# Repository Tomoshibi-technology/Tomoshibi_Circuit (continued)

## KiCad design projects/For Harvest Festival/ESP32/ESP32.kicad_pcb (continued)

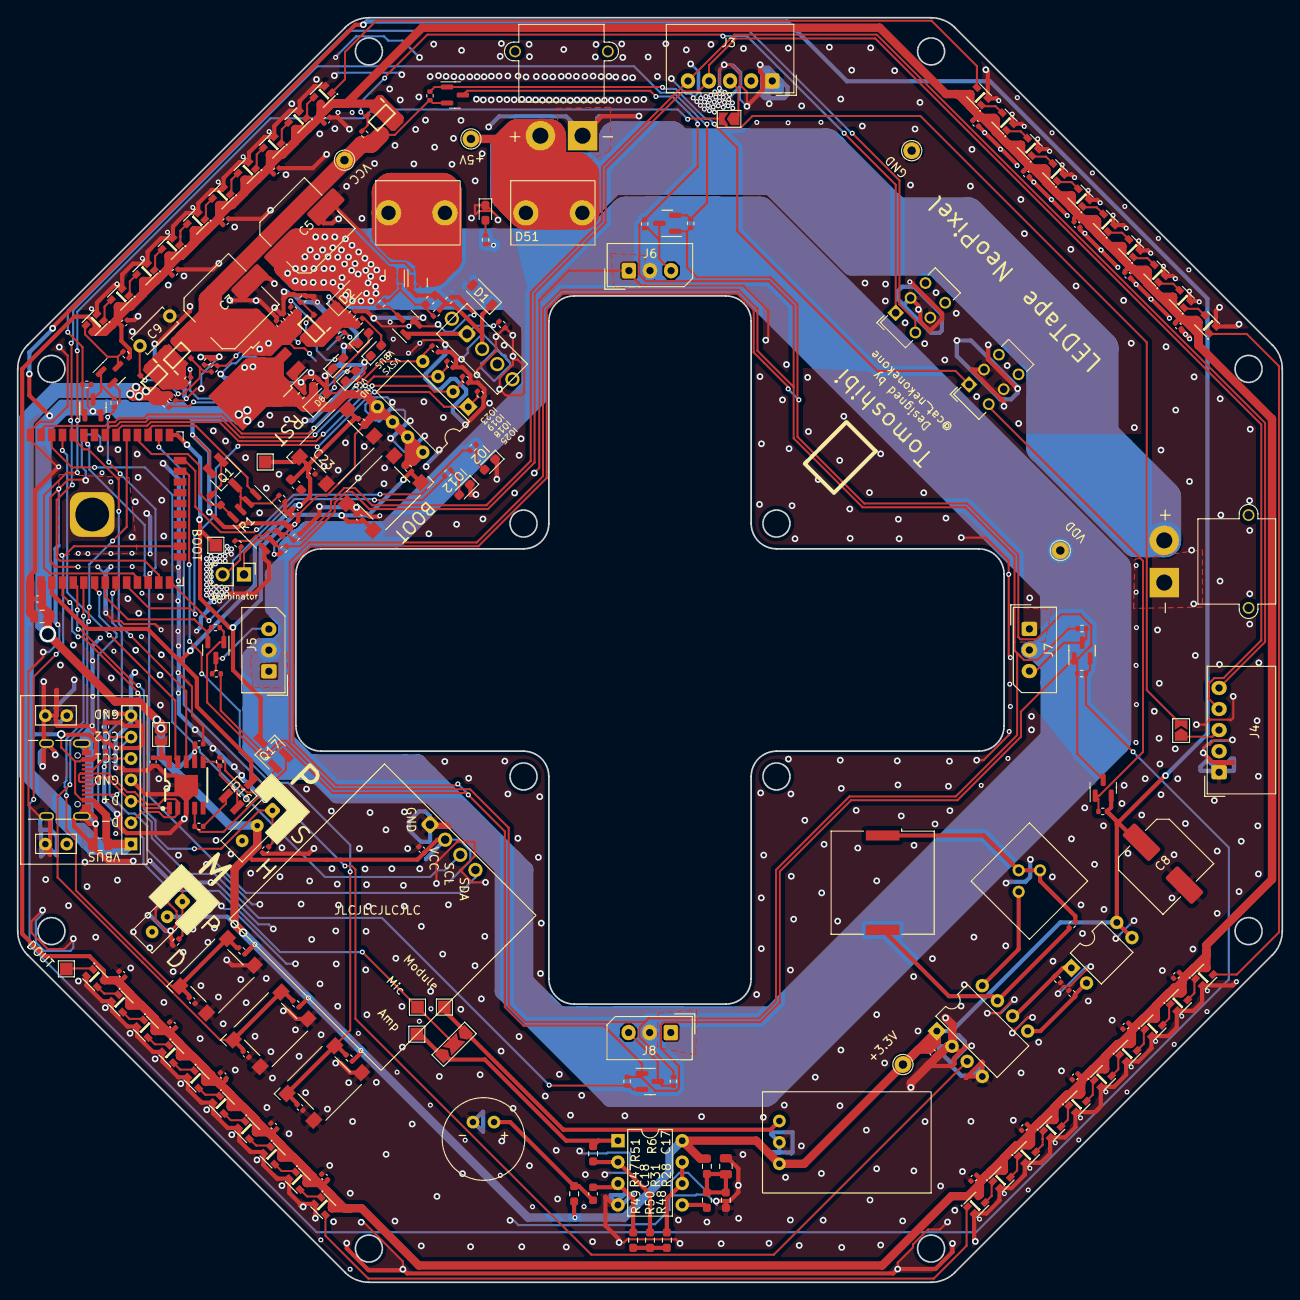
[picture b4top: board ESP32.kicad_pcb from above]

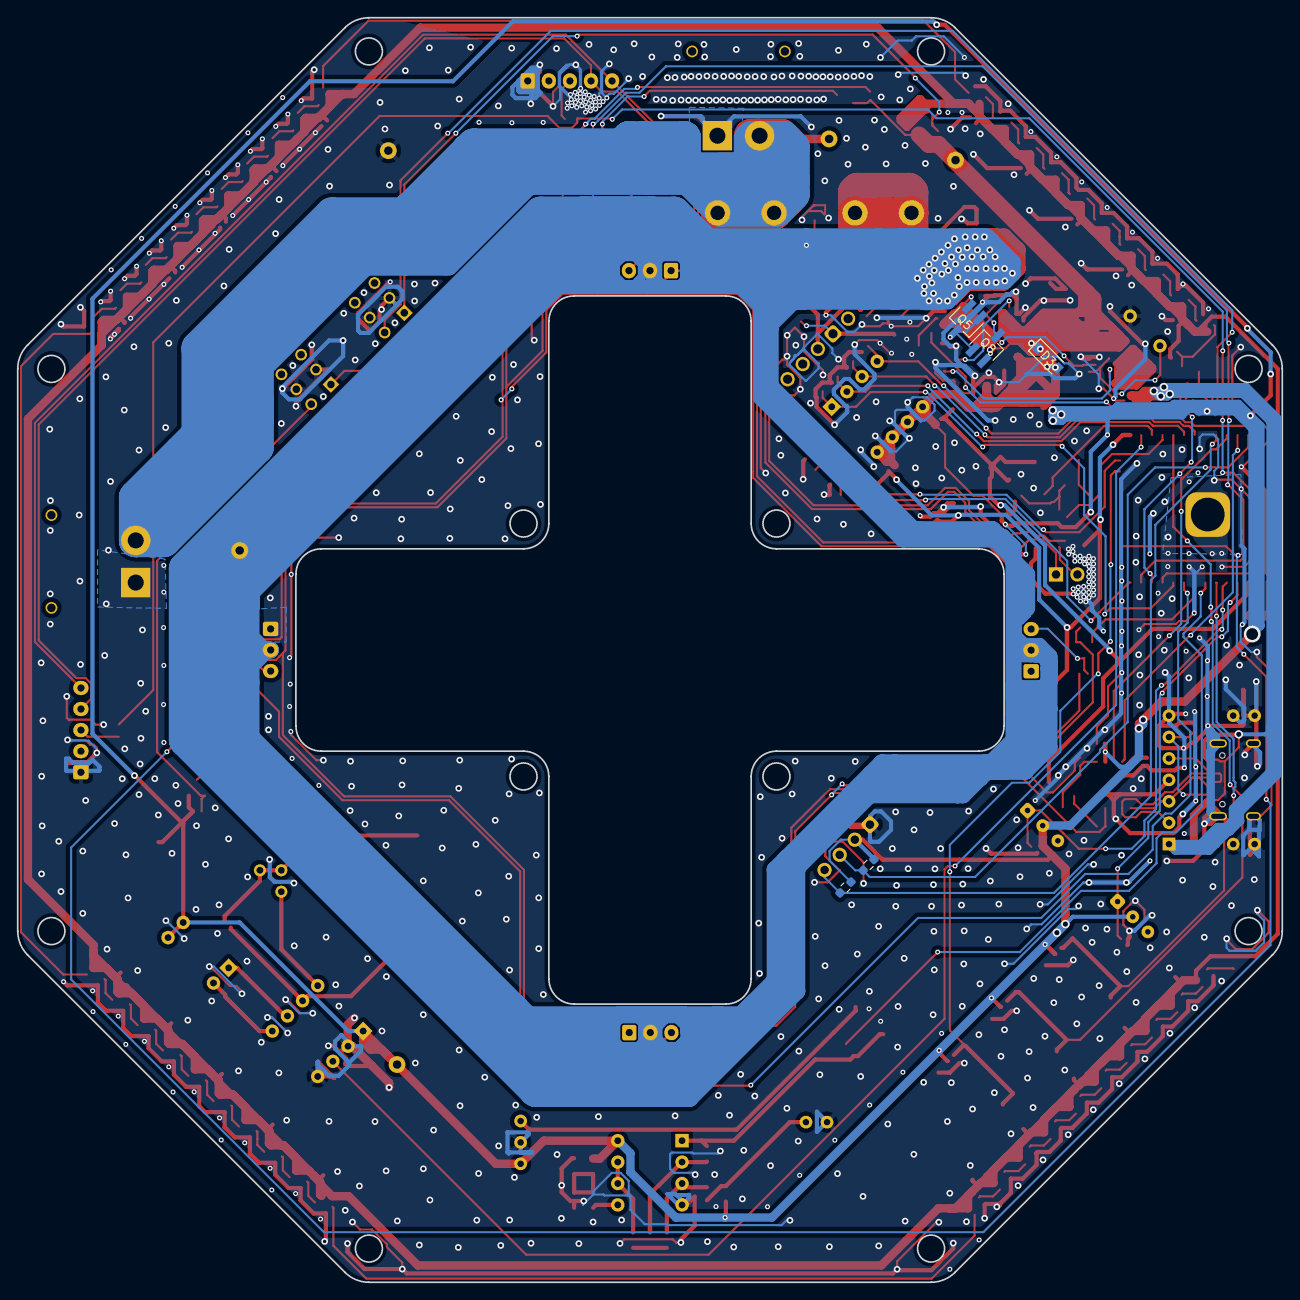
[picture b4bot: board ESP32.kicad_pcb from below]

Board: 2 copper layers, 150.0 x 150.0 mm, 230 parts (5 on the bottom side), 133 nets.

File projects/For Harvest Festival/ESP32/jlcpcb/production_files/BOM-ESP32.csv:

Comment,Designator,Footprint,LCSC
1k,"R12,R17,R20,R21,R22,R23,R25,R29,R30,R67",R_0402_1005Metric,C11702
PMN48XP,"Q2,Q4",UDFN6,C146307
10uF,"C1,C17",C_0805_2012Metric,C15850
4.7uF,"C18,C6",C_0603_1608Metric,C19666
R,"R31,R48",R_0603_1608Metric_Pad0.98x0.95mm_HandSolder,C21189
1k,R50,R_0603_1608Metric_Pad0.98x0.95mm_HandSolder,C21190
7.5k,R1,R_0603_1608Metric,C23234
120,R9,R_0402_1005Metric,C25079
10k,"R10,R11,R13,R14,R15,R16,R18,R19,R24,R26,R27,R32,R35,R36,R37,R38,R39,R40,R41,R42,R43,R44,R45,R46,R5,R52,R53,R54,R55,R56,R57,R58,R59,R60,R61,R62,R63,R64,R65",R_0402_1005Metric,C25744
20k,R3,R_0402_1005Metric,C25765
100k,"R28,R49,R51,R6",R_0603_1608Metric_Pad0.98x0.95mm_HandSolder,C25803
R,"R33,R34",R_0603_1608Metric_Pad0.98x0.95mm_HandSolder,C25804
2.2k,"R7,R8",R_0402_1005Metric,C25879
5.1k,"R2,R4",R_0402_1005Metric,C25905
Q_PMOS_GSD,"Q10,Q11,Q19",SOT-23,C266796
Q_NMOS_GSD,"Q12,Q13,Q14,Q15,Q20,Q3",SOT-23,C2844873
WS2812C-2020-V1,"D11,D12,D13,D14,D15,D16,D17,D18,D19,D20,D21,D22,D23,D24,D25,D26,D27,D28,D29,D30,D31,D32,D33,D34,D35,D36,D37,D38,D39,D40,D41,D42,D43,D44,D45,D46,D47,D48,D49,D50",WS2812C-2020-V1,C2976072
0.1uF,"C13,C14,C15,C16,C2,C20,C21,C22,C24,C25,C26,C27,C28,C29,C3,C30,C31,C32,C33,C34,C35,C36,C37,C38,C39,C4,C40,C41,C42,C43",C_0402_1005Metric,C307331
2.2k,R47,R_0603_1608Metric_Pad0.98x0.95mm_HandSolder,C4190
22uF,C19,C_0805_2012Metric,C45783
1uF,"C10,C11,C12",C_0402_1005Metric,C52923
MAX3485,U1,SOP-8_3.9x4.9mm_P1.27mm,C558792
CH340K,U2,CH340K,C968586
Jumper_2_Open,JP1,PinHeader_1x02_P2.54mm_Vertical,
MountingHole_Pad,H2,TestPoint_Pad_1.5x1.5mm,
MountingHole_Pad,H1,TestPoint_Pad_1.5x1.5mm,
SW_SPST,SW5,SW_SPST_Omron_B3FS-100xP,
Conn_01x03_Female,J7,Molex_SPOX_5267-03A_1x03_P2.50mm_Vertical,
Conn_01x03_Female,J5,Molex_SPOX_5267-03A_1x03_P2.50mm_Vertical,
Q_NPN_BEC,Q17,SC-59_Handsoldering,
MountingHole_Pad,H7,TestPoint_Pad_1.5x1.5mm,
LED,D10,LED_0603_1608Metric_Pad1.05x0.95mm_HandSolder,
Conn_01x05_Female,J3,Molex_SPOX_5268-05A_1x05_P2.50mm_Horizontal,
SW_SPST,SW7,SW_SPST_Omron_B3FS-100xP,
LED,D9,LED_0603_1608Metric_Pad1.05x0.95mm_HandSolder,
LED,D7,LED_0603_1608Metric_Pad1.05x0.95mm_HandSolder,
PMN48XP,Q7,SSM6J808R,
D,D1,D_SOD-123,
MountingHole_Pad,H5,TestPoint_Pad_1.5x1.5mm,
LED,D4,LED_0603_1608Metric_Pad1.05x0.95mm_HandSolder,
AE-MICAMP,U7,AE-MICAMP,
470uF,C8,C_Elec_8x10.2,
Speaker,LS1,Buzzer_Murata_PKLCS1212E,
ADJ_ST,C9,C_Disc_D5.0mm_W2.5mm_P5.00mm,
Jumper_2_Open,JP3,SolderJumper-2_P1.3mm_Open_TrianglePad1.0x1.5mm,
Conn_01x02_Female,J9,AMASS_XT30PW-M_1x02_P2.50mm_Horizontal,
SW_DIP_x04,SW11,DIP-8_W7.62mm,
Conn_01x05_Female,J4,Molex_SPOX_5268-05A_1x05_P2.50mm_Horizontal,
Microphone_Condenser,MK1,C9767,
SW_DIP_x02,SW2,DIP-4_W7.62mm,
Q_NPN_BEC,Q16,SC-59_Handsoldering,
D_Zener,D8,D_SOD-323_HandSoldering,
TestPoint,TP5,TestPoint_THTPad_D2.0mm_Drill1.0mm,
NJM4558,U6,DIP-8_W7.62mm,
TestPoint,TP4,TestPoint_THTPad_D2.0mm_Drill1.0mm,
Jumper_2_Open,JP4,SolderJumper-2_P1.3mm_Open_TrianglePad1.0x1.5mm,
C,C23,C_0603_1608Metric_Pad1.08x0.95mm_HandSolder,
LED,D6,LED_0603_1608Metric_Pad1.05x0.95mm_HandSolder,
SW_SPDT,SW3,3P_SPDT_SlideSwitch,
470uF,C5,C_Elec_8x10.2,
R_Potentiometer,RV1,TSR-3386K,
USB_C_Receptacle_USB2.0,J10,USB_C_Receptacle_GCT_USB4105-xx-A_16P_TopMnt_Horizontal,
TestPoint,TP3,TestPoint_THTPad_D2.0mm_Drill1.0mm,
MountingHole_Pad,H8,TestPoint_Pad_1.5x1.5mm,
Jumper_2_Open,JP2,SolderJumper-2_P1.3mm_Open_TrianglePad1.0x1.5mm,
Conn_01x03_Female,J8,Molex_SPOX_5267-03A_1x03_P2.50mm_Vertical,
Q_PNP_BEC,Q1,SC-59_Handsoldering,
TestPoint,TP1,TestPoint_THTPad_D2.0mm_Drill1.0mm,
OLED_akitsuki,U5,128×64_OLED_White,
SW_SPST,SW10,SW_SPST_Omron_B3FS-100xP,
TestPoint,TP2,TestPoint_THTPad_D2.0mm_Drill1.0mm,
SW_SPDT,SW1,3P_SPDT_5Pin_ToggleSwitch,
ESP32-WROOM-32,U8,ESP32-WROOM-32,
SW_SPST,SW6,SW_SPST_Omron_B3FS-100xP,
MountingHole_Pad,H6,TestPoint_Pad_1.5x1.5mm,
AMS1117CD-3.3,U3,TO-252-3_TabPin2,
Fuse,F1,FUC_03A,
USB_C_Receptacle_USB2.0,J1,USB_C(simple),
470uF,C7,C_Elec_8x10.2,
Conn_01x03_Female,J6,Molex_SPOX_5267-03A_1x03_P2.50mm_Vertical,
LED,D51,LED_0603_1608Metric_Pad1.05x0.95mm_HandSolder,
SolderJumper_3_Open,JP5,SolderJumper-3_P2.0mm_Open_TrianglePad1.0x1.5mm_NumberLabels,
Conn_01x02_Female,J2,AMASS_XT30PW-M_1x02_P2.50mm_Horizontal,
SW_DPDT_x2,SW8,SW_CuK_JS202011CQN_DPDT_Straight,
LED,D5,LED_0603_1608Metric_Pad1.05x0.95mm_HandSolder,
SW_SPDT,SW4,3P_SPDT_SlideSwitch,
NJU72501_Module,U4,DIP-8_W7.62mm,
PMN48XP,Q18,SSM6J808R,
D_Schottky,D2,D_SOD-123,
SW_DPDT_x2,SW12,SW_CuK_JS202011CQN_DPDT_Straight,
PMN48XP,Q6,SSM6J808R,
SW_SPST,SW9,SW_SPST_Omron_B3FS-100xP,
PMN48XP,Q9,SSM6J808R,
Q_PNP_BEC,Q8,SC-59_Handsoldering,
Q_PNP_BEC,Q5,SC-59_Handsoldering,
D,D3,D_SOD-123,

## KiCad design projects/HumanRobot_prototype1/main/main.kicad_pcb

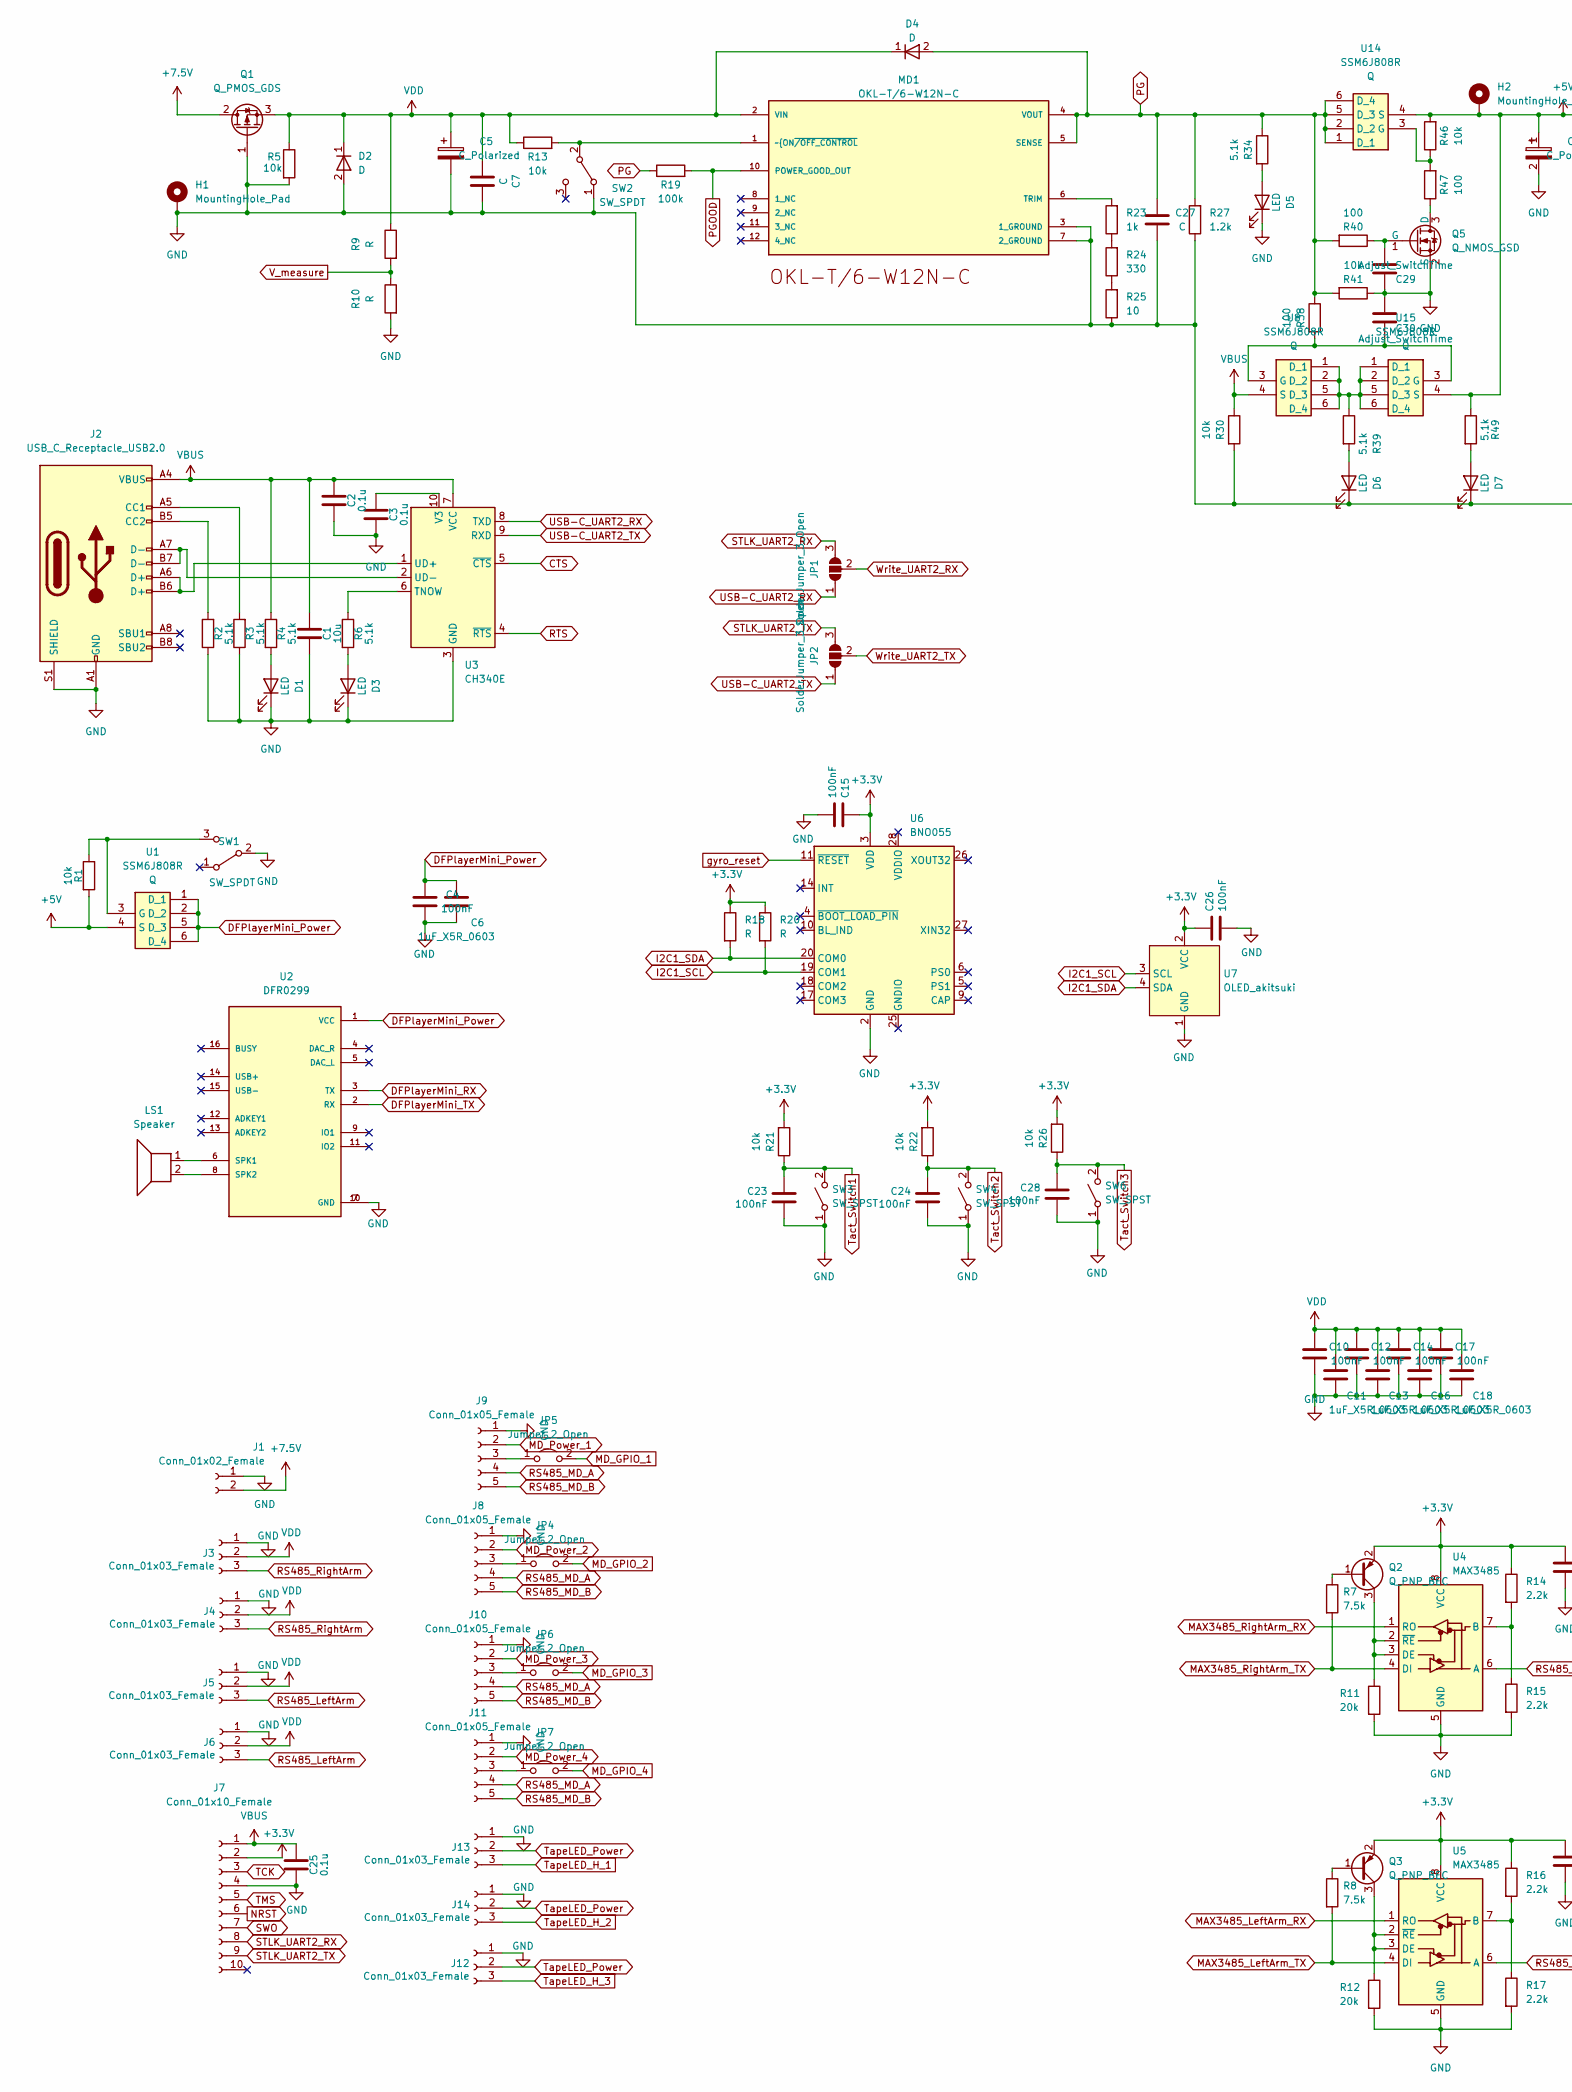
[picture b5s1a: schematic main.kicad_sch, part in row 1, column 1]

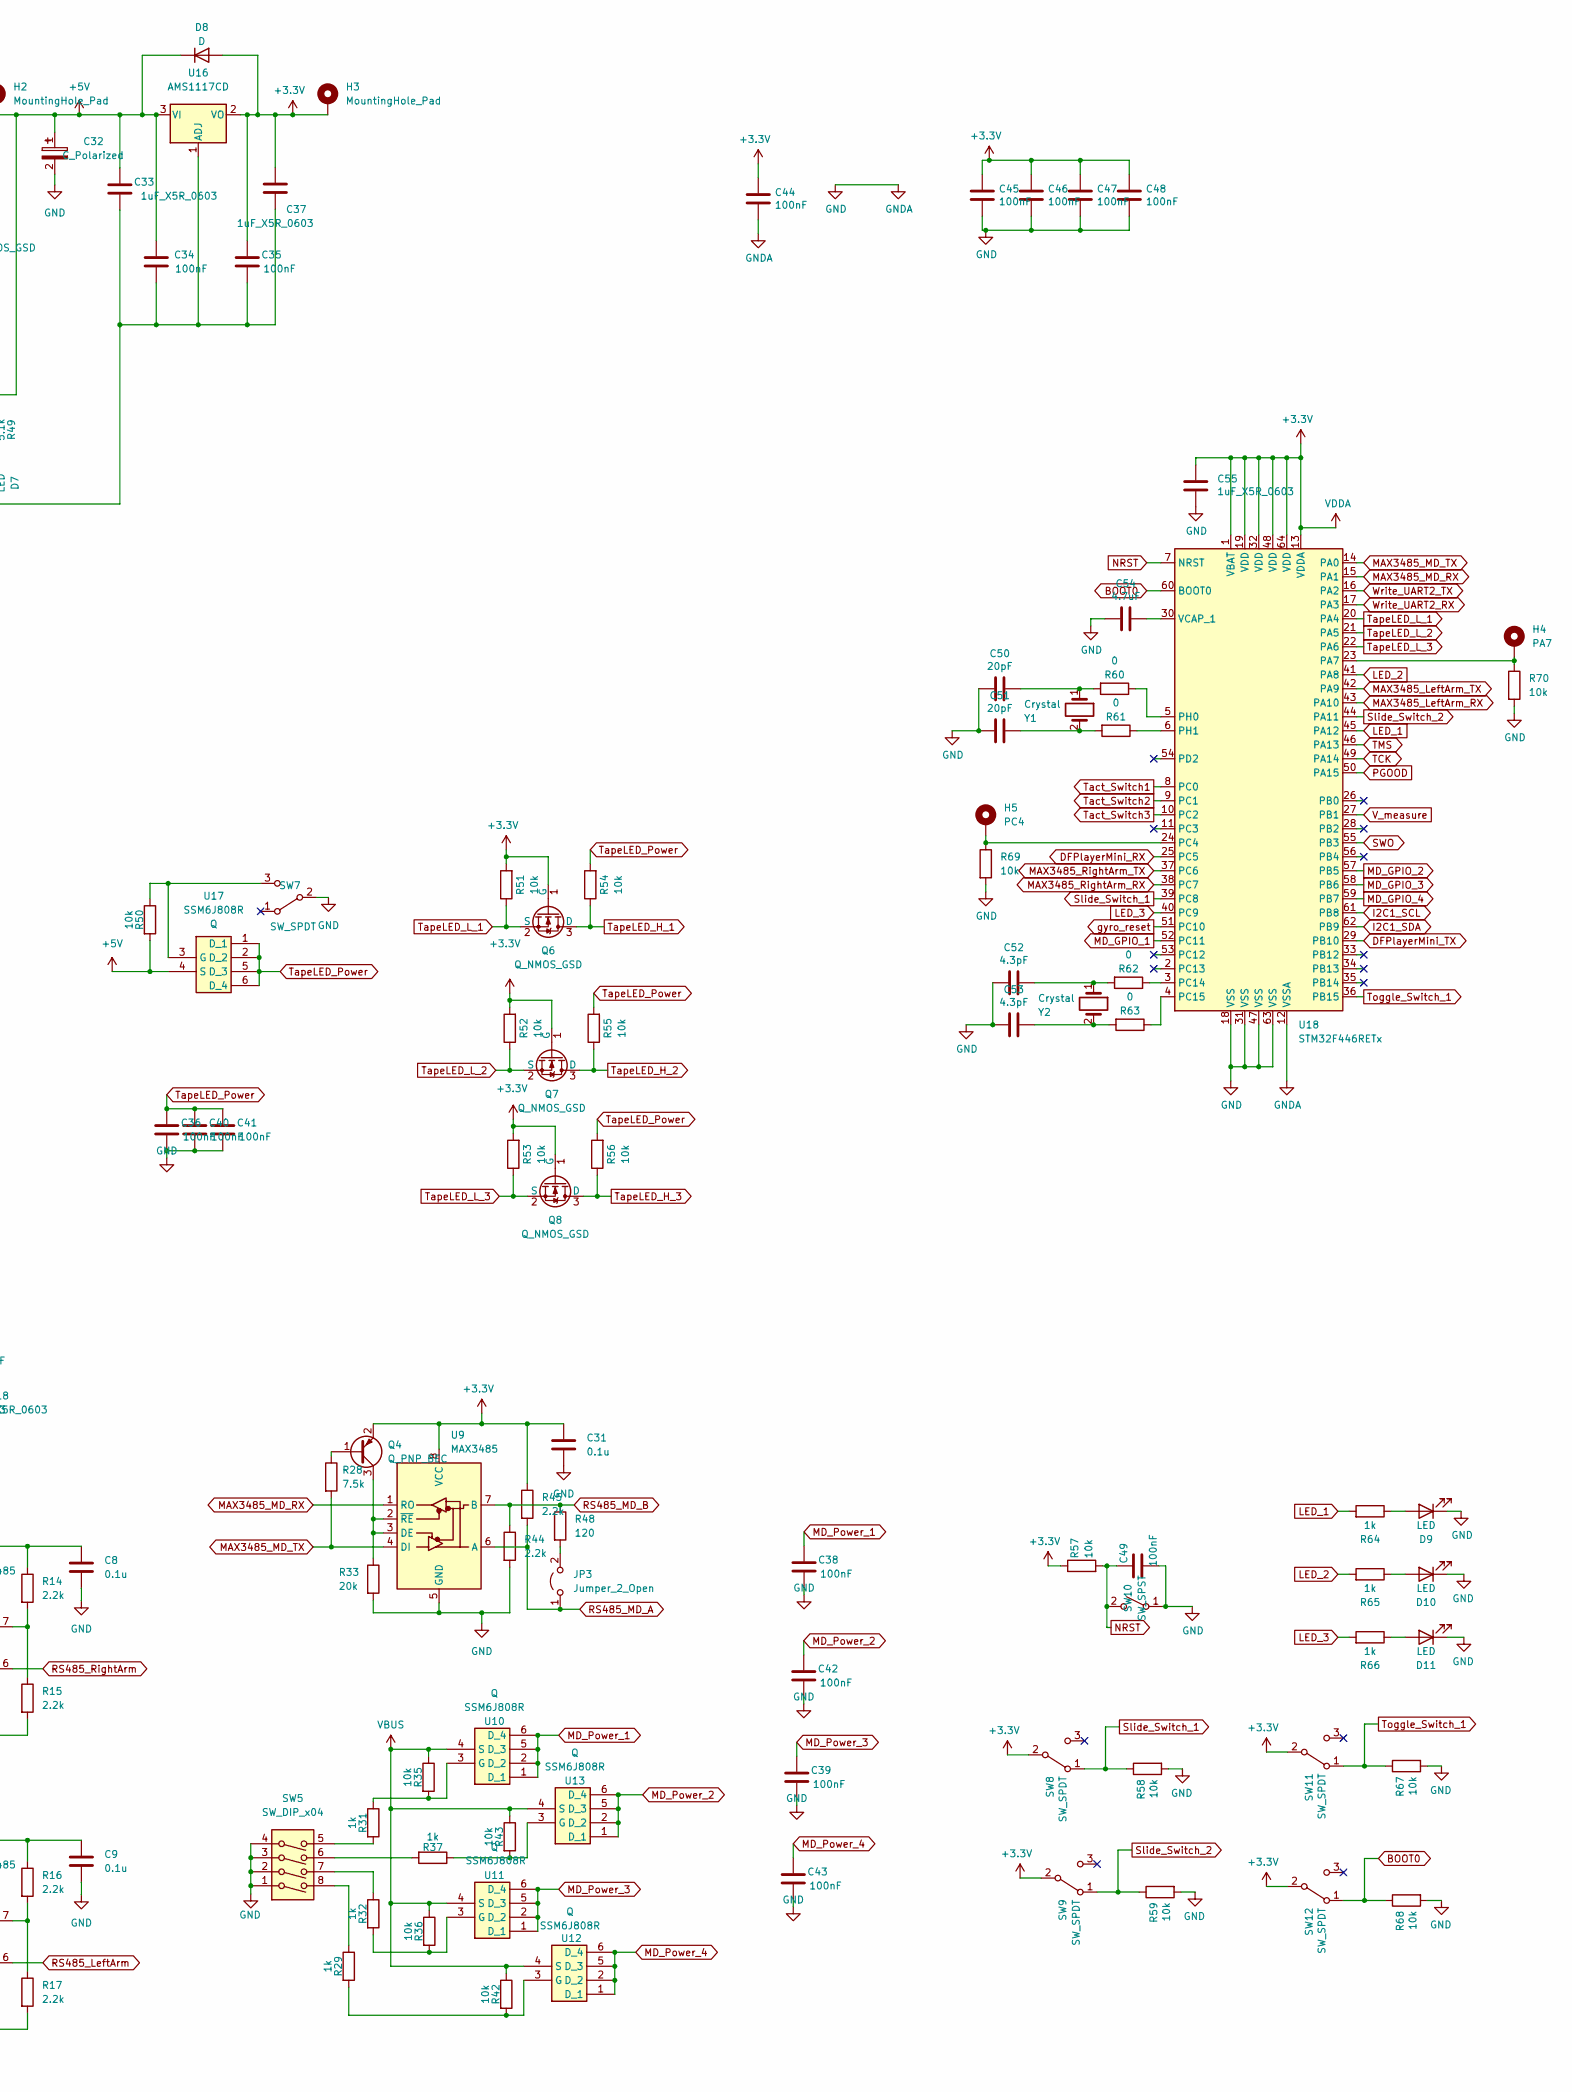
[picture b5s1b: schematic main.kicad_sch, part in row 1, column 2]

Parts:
C1: 10u; C_0805_2012Metric_Pad1.18x1.45mm_HandSolder
C2, C3, C8, C9, C25, C31: 0.1u; C_0603_1608Metric_Pad1.08x0.95mm_HandSolder
C4, C10, C12, C14, C15, C17, C23, C24, C26, C28, C34, C35, C36, C38, C39, C40, C41, C42, C43, C44, C45, C46, C47, C48, C49: 100nF; C_0603_1608Metric_Pad1.08x0.95mm_HandSolder
C5, C32: C_Polarized; C_Elec_8x10.2
C6, C11, C13, C16, C18, C33, C37, C55: 1uF_X5R_0603; C_0603_1608Metric_Pad1.08x0.95mm_HandSolder
C7: C; CAPC3225X270N
C27: C; CAPC3216X180N
C29, C30: Adjust_SwitchTime; C_Disc_D5.0mm_W2.5mm_P5.00mm
C50, C51: 20pF; C_Disc_D5.0mm_W2.5mm_P5.00mm
C52, C53: 4.3pF; C_Disc_D5.0mm_W2.5mm_P5.00mm
C54: 4.7uF; C_0805_2012Metric_Pad1.18x1.45mm_HandSolder
D1, D3, D5, D6, D7, D9, D10, D11: LED; LED_0603_1608Metric_Pad1.05x0.95mm_HandSolder
D2, D4, D8: D; D_SOD-123
H1, H2, H3: MountingHole_Pad; TestPoint_Pad_3.0x3.0mm
H4: PA7; TestPoint_Pad_3.0x3.0mm
H5: PC4; TestPoint_Pad_3.0x3.0mm
J1: Conn_01x02_Female; AMASS_XT30PW-M_1x02_P2.50mm_Horizontal
J2: USB_C_Receptacle_USB2.0; USB_C(simple)
J3, J4, J5, J6, J12, J13, J14: Conn_01x03_Female; Molex_SPOX_5268-03A_1x03_P2.50mm_Horizontal
J7: Conn_01x10_Female; IDC-Header_2x05_P2.54mm_Horizontal
J8, J9, J10, J11: Conn_01x05_Female; Molex_SPOX_5268-05A_1x05_P2.50mm_Horizontal
JP1, JP2: SolderJumper_3_Open; SolderJumper-3_P2.0mm_Open_TrianglePad1.0x1.5mm_NumberLabels
JP3: Jumper_2_Open; PinHeader_1x02_P2.54mm_Vertical
JP4, JP5, JP6, JP7: Jumper_2_Open; SolderJumper-2_P1.3mm_Open_TrianglePad1.0x1.5mm
LS1: Speaker; Buzzer_Murata_PKMCS0909E
MD1: OKL-T/6-W12N-C; MURATA_OKL-T-6-W12N-C; MOUSER_PART_NUMBER 580-OKL-T/6-W12N-C
Q1: Q_PMOS_GDS; TO-251-3_Vertical
Q2, Q3, Q4: Q_PNP_BEC; SC-59
Q5, Q6, Q7, Q8: Q_NMOS_GSD; SOT-23_Handsoldering
R1, R5, R13, R21, R22, R26, R30, R35, R36, R41, R42, R43, R46, R50, R51, R52, R53, R54, R55, R56, R57, R58, R59, R67, R68, R69, R70: 10k; R_0603_1608Metric_Pad0.98x0.95mm_HandSolder
R2, R3, R4, R6, R34, R39, R49: 5.1k; R_0603_1608Metric_Pad0.98x0.95mm_HandSolder
R7, R8, R28: 7.5k; R_0603_1608Metric_Pad0.98x0.95mm_HandSolder
R9, R10, R18, R20: R; R_0603_1608Metric_Pad0.98x0.95mm_HandSolder
R11, R12, R33: 20k; R_0603_1608Metric_Pad0.98x0.95mm_HandSolder
R14, R15, R16, R17, R44, R45: 2.2k; R_0603_1608Metric_Pad0.98x0.95mm_HandSolder
R19: 100k; R_0603_1608Metric_Pad0.98x0.95mm_HandSolder
R23, R29, R31, R32, R37, R64, R65, R66: 1k; R_0603_1608Metric_Pad0.98x0.95mm_HandSolder
R24: 330; R_0603_1608Metric_Pad0.98x0.95mm_HandSolder
R25: 10; R_0603_1608Metric_Pad0.98x0.95mm_HandSolder
R27: 1.2k; R_0603_1608Metric_Pad0.98x0.95mm_HandSolder
R38, R40, R47: 100; R_0603_1608Metric_Pad0.98x0.95mm_HandSolder
R48: 120; R_0603_1608Metric_Pad0.98x0.95mm_HandSolder
R60, R61, R62, R63: 0; R_0603_1608Metric_Pad0.98x0.95mm_HandSolder
SW1, SW2, SW7, SW8, SW9, SW12: SW_SPDT; 3P_SPDT_SlideSwitch
SW3, SW4, SW6, SW10: SW_SPST; SW_SPST_Omron_B3FS-100xP
SW5: SW_DIP_x04; DIP-8_W7.62mm
SW11: SW_SPDT; 3P_SPDT_5Pin_ToggleSwitch
U1, U8, U10, U11, U12, U13, U14, U15, U17: SSM6J808R; Mouser Part Number 757-SSM6K809RLXHF
U2: DFR0299; MODULE_DFR0299
U3: CH340E; MSOP-10_3x3mm_P0.5mm
U4, U5, U9: MAX3485; SOP-8_3.9x4.9mm_P1.27mm
U6: BNO055
U7: OLED_akitsuki; 128×64_OLED_White
U16: AMS1117CD; TO-252-3_TabPin2
U18: STM32F446RETx; LQFP-64_10x10mm_P0.5mm
Y1, Y2: Crystal; Crystal_HC18-U_Vertical

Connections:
+3.3V: C8.1, C9.1, C15.1, C26.1, C31.1, C35.2, C37.1, C44.2, C45.2, C46.2, C47.2, C48.2, C55.1, D8.2 (A), H3.1, J7.2, Q2.2 (E), Q3.2 (E), Q4.2 (E), Q6.1 (G), Q7.1 (G), Q8.1 (G), R14.1, R16.1, R18.1, R20.1, R21.2, R22.2, R26.2, R45.1, R51.2, R52.2, R53.2, R57.1, SW8.2 (B), SW9.2 (B), SW11.2 (B), SW12.2 (B), U4.8 (VCC), U5.8 (VCC), U6.3 (VDD), U7.2 (VCC), U9.8 (VCC), U16.2 (VO), U18.1 (VBAT), U18.13 (VDDA), U18.19 (VDD), U18.32 (VDD), U18.48 (VDD), U18.64 (VDD)
+5V: C32.1, C33.2, C34.1, D8.1 (K), H2.1, R1.2, R46.2, R49.1, R50.2, U1.4 (S), U14.4 (S), U15.4 (S), U16.3 (VI), U17.4 (S)
+7.5V: J1.2, Q1.2 (D)
BOOT0: R68.1, SW12.1 (A), U18.60 (BOOT0)
CTS: U3.5 (~CTS)
DFPlayerMini_Power: C4.2, C6.1, U1.1 (D_1), U1.2 (D_2), U1.5 (D_3), U1.6 (D_4), U2.1 (VCC)
DFPlayerMini_RX: U2.3 (TX), U18.25 (PC5)
DFPlayerMini_TX: U2.2 (RX), U18.29 (PB10)
GND: C1.1, C2.1, C3.1, C4.1, C5.2, C6.2, C7.1, C8.2, C9.2, C10.1, C11.2, C12.1, C13.2, C14.1, C15.2, C16.2, C17.1, C18.2, C23.2, C24.2, C25.1, C26.2, C27.1, C28.2, C29.2, C30.1, C31.2, C32.2, C33.1, C34.2, C35.1, C36.1, C37.2, C38.1, C39.1, C40.1, C41.1, C42.1, C43.1, C44.1, C45.1, C46.1, C47.1, C48.1, C49.2, C50.1, C51.1, C52.1, C53.1, C54.1, C55.2, D1.1 (K), D2.2 (A), D3.1 (K), D5.1 (K), D6.1 (K), D7.1 (K), D9.1 (K), D10.1 (K), D11.1 (K), H1.1, J1.1, J2.A1 (GND), J2.A12 (GND), J2.B1 (GND), J2.B12 (GND), J2.S1 (SHIELD), J3.1, J4.1, J5.1, J6.1, J7.4, J8.1, J9.1, J10.1, J11.1, J12.1, J13.1, J14.1, MD1.3 (1_GROUND), MD1.7 (2_GROUND), Q1.1 (G), Q5.2 (S), R2.1, R3.1, R5.2, R10.2, R11.2, R12.2, R15.2, R17.2, R25.1, R27.1, R30.2, R33.2, R41.1, R44.2, R58.2, R59.2, R67.2, R68.2, R69.2, R70.2, SW1.2 (B), SW2.1 (A), SW3.1 (A), SW4.1 (A), SW5.1, SW5.2, SW5.3, SW5.4, SW6.1 (A), SW7.2 (B), SW10.1 (A), U2.7 (GND), U2.10 (GND), U3.3 (GND), U4.5 (GND), U5.5 (GND), U6.2 (GND), U7.1 (GND), U9.5 (GND), U16.1 (ADJ), U18.12 (VSSA), U18.18 (VSS), U18.31 (VSS), U18.47 (VSS), U18.63 (VSS)
I2C1_SCL: R20.2, U6.19 (COM1), U7.3 (SCL), U18.61 (PB8)
I2C1_SDA: R18.2, U6.20 (COM0), U7.4 (SDA), U18.62 (PB9)
LED_1: R64.2, U18.45 (PA12)
LED_2: R65.2, U18.41 (PA8)
LED_3: R66.2, U18.40 (PC9)
MAX3485_LeftArm_RX: U5.1 (RO), U18.43 (PA10)
MAX3485_LeftArm_TX: R8.2, U5.4 (DI), U18.42 (PA9)
MAX3485_MD_RX: U9.1 (RO), U18.15 (PA1)
MAX3485_MD_TX: R28.2, U9.4 (DI), U18.14 (PA0)
MAX3485_RightArm_RX: U4.1 (RO), U18.38 (PC7)
MAX3485_RightArm_TX: R7.2, U4.4 (DI), U18.37 (PC6)
MD_GPIO_1: JP5.2 (B), U18.52 (PC11)
MD_GPIO_2: JP4.2 (B), U18.57 (PB5)
MD_GPIO_3: JP6.2 (B), U18.58 (PB6)
MD_GPIO_4: JP7.2 (B), U18.59 (PB7)
MD_Power_1: C38.2, J9.2, U10.1 (D_1), U10.2 (D_2), U10.5 (D_3), U10.6 (D_4)
MD_Power_2: C42.2, J8.2, U13.1 (D_1), U13.2 (D_2), U13.5 (D_3), U13.6 (D_4)
MD_Power_3: C39.2, J10.2, U11.1 (D_1), U11.2 (D_2), U11.5 (D_3), U11.6 (D_4)
MD_Power_4: C43.2, J11.2, U12.1 (D_1), U12.2 (D_2), U12.5 (D_3), U12.6 (D_4)
NRST: C49.1, J7.6, R57.2, SW10.2 (B), U18.7 (NRST)
unnamed: C3.2, U3.10 (V3)
unnamed: C29.1, Q5.1 (G), R40.1
unnamed: C30.2, R38.2, U8.3 (G), U15.3 (G)
unnamed: C50.2, R60.2, Y1.1
unnamed: C51.2, R61.2, Y1.2
unnamed: C52.2, R62.2, Y2.1
unnamed: C53.2, R63.2, Y2.2
unnamed: C54.2, U18.30 (VCAP_1)
unnamed: D1.2 (A), R4.2
unnamed: D3.2 (A), R6.2
unnamed: D5.2 (A), R34.2
unnamed: D6.2 (A), R39.2
unnamed: D7.2 (A), R49.2
unnamed: D9.2 (A), R64.1
unnamed: D10.2 (A), R65.1
unnamed: D11.2 (A), R66.1
unnamed: H4.1, R70.1, U18.23 (PA7)
unnamed: H5.1, R69.1, U18.24 (PC4)
unnamed: J2.A5 (CC1), R3.2
unnamed: J2.A6 (D+), J2.B6 (D+), U3.1 (UD+)
unnamed: J2.A7 (D-), J2.B7 (D-), U3.2 (UD-)
unnamed: J2.B5 (CC2), R2.2
unnamed: J8.3, JP4.1 (A)
unnamed: J9.3, JP5.1 (A)
unnamed: J10.3, JP6.1 (A)
unnamed: J11.3, JP7.1 (A)
unnamed: JP3.2 (B), R48.2
unnamed: LS1.1, U2.6 (SPK1)
unnamed: LS1.2, U2.8 (SPK2)
unnamed: MD1.1 (~ON~{/OFF_CONTROL), R13.2, SW2.2 (B)
unnamed: MD1.6 (TRIM), R23.2
unnamed: Q2.1 (B), R7.1
unnamed: Q2.3 (C), R11.1, U4.2 (~RE), U4.3 (DE)
unnamed: Q3.1 (B), R8.1
unnamed: Q3.3 (C), R12.1, U5.2 (~RE), U5.3 (DE)
unnamed: Q4.1 (B), R28.1
unnamed: Q4.3 (C), R33.1, U9.2 (~RE), U9.3 (DE)
unnamed: Q5.3 (D), R47.1
unnamed: R1.1, SW1.3 (C), U1.3 (G)
unnamed: R6.1, U3.6 (TNOW)
unnamed: R14.2, R15.1, U4.7 (B)
unnamed: R16.2, R17.1, U5.7 (B)
unnamed: R23.1, R24.2
unnamed: R24.1, R25.2
unnamed: R29.1, SW5.8
unnamed: R29.2, R42.2, U12.3 (G)
unnamed: R31.1, R35.2, U10.3 (G)
unnamed: R31.2, SW5.5
unnamed: R32.1, SW5.7
unnamed: R32.2, R36.2, U11.3 (G)
unnamed: R37.1, R43.2, U13.3 (G)
unnamed: R37.2, SW5.6
unnamed: R39.1, U8.1 (D_1), U8.2 (D_2), U8.5 (D_3), U8.6 (D_4), U15.1 (D_1), U15.2 (D_2), U15.5 (D_3), U15.6 (D_4)
unnamed: R46.1, R47.2, U14.3 (G)
unnamed: R50.1, SW7.3 (C), U17.3 (G)
unnamed: R60.1, U18.5 (PH0)
unnamed: R61.1, U18.6 (PH1)
unnamed: R62.1, U18.3 (PC14)
unnamed: R63.1, U18.4 (PC15)
PG: C27.2, D4.2 (A), MD1.4 (VOUT), MD1.5 (SENSE), R19.1, R27.2, R34.1, R38.1, R40.2, R41.2, U14.1 (D_1), U14.2 (D_2), U14.5 (D_3), U14.6 (D_4)
PGOOD: MD1.10 (POWER_GOOD_OUT), R19.2, U18.50 (PA15)
RS485_LeftArm: J5.3, J6.3, U5.6 (A)
RS485_MD_A: J8.4, J9.4, J10.4, J11.4, JP3.1 (A), R45.2, U9.6 (A)
RS485_MD_B: J8.5, J9.5, J10.5, J11.5, R44.1, R48.1, U9.7 (B)
RS485_RightArm: J3.3, J4.3, U4.6 (A)
RTS: U3.4 (~RTS)
STLK_UART2_RX: J7.8, JP1.3 (B)
STLK_UART2_TX: J7.9, JP2.3 (B)
SWO: J7.7, U18.55 (PB3)
Slide_Switch_1: R58.1, SW8.1 (A), U18.39 (PC8)
Slide_Switch_2: R59.1, SW9.1 (A), U18.44 (PA11)
TCK: J7.3, U18.49 (PA14)
TMS: J7.5, U18.46 (PA13)
Tact_Switch1: C23.1, R21.1, SW3.2 (B), U18.8 (PC0)
Tact_Switch2: C24.1, R22.1, SW4.2 (B), U18.9 (PC1)
Tact_Switch3: C28.1, R26.1, SW6.2 (B), U18.10 (PC2)
TapeLED_H_1: J13.3, Q6.3 (D), R54.1
TapeLED_H_2: J14.3, Q7.3 (D), R55.1
TapeLED_H_3: J12.3, Q8.3 (D), R56.1
TapeLED_L_1: Q6.2 (S), R51.1, U18.20 (PA4)
TapeLED_L_2: Q7.2 (S), R52.1, U18.21 (PA5)
TapeLED_L_3: Q8.2 (S), R53.1, U18.22 (PA6)
TapeLED_Power: C36.2, C40.2, C41.2, J12.2, J13.2, J14.2, R54.2, R55.2, R56.2, U17.1 (D_1), U17.2 (D_2), U17.5 (D_3), U17.6 (D_4)
Toggle_Switch_1: R67.1, SW11.1 (A), U18.36 (PB15)
USB-C_UART2_RX: JP1.1 (A), U3.8 (TXD)
USB-C_UART2_TX: JP2.1 (A), U3.9 (RXD)
VBUS: C1.2, C2.2, C25.2, J2.A4 (VBUS), J2.A9 (VBUS), J2.B4 (VBUS), J2.B9 (VBUS), J7.1, R4.1, R30.1, R35.1, R36.1, R42.1, R43.1, U3.7 (VCC), U8.4 (S), U10.4 (S), U11.4 (S), U12.4 (S), U13.4 (S)
VDD: C5.1, C7.2, C10.2, C11.1, C12.2, C13.1, C14.2, C16.1, C17.2, C18.1, D2.1 (K), D4.1 (K), J3.2, J4.2, J5.2, J6.2, MD1.2 (VIN), Q1.3 (S), R5.1, R9.1, R13.1
V_measure: R9.2, R10.1, U18.27 (PB1)
Write_UART2_RX: JP1.2 (C), U18.17 (PA3)
Write_UART2_TX: JP2.2 (C), U18.16 (PA2)
gyro_reset: U6.11 (~RESET), U18.51 (PC10)

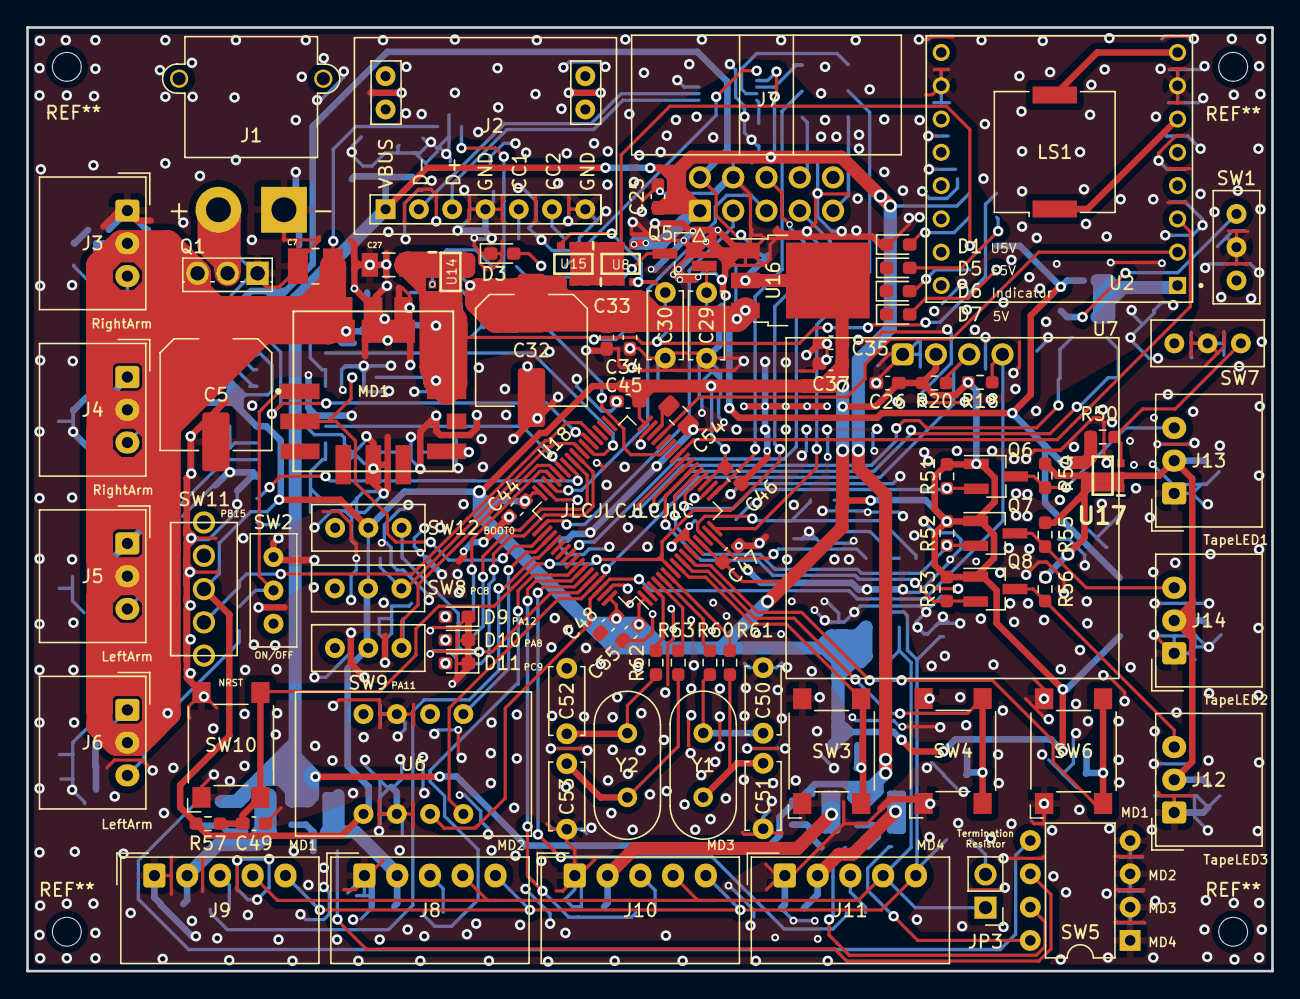
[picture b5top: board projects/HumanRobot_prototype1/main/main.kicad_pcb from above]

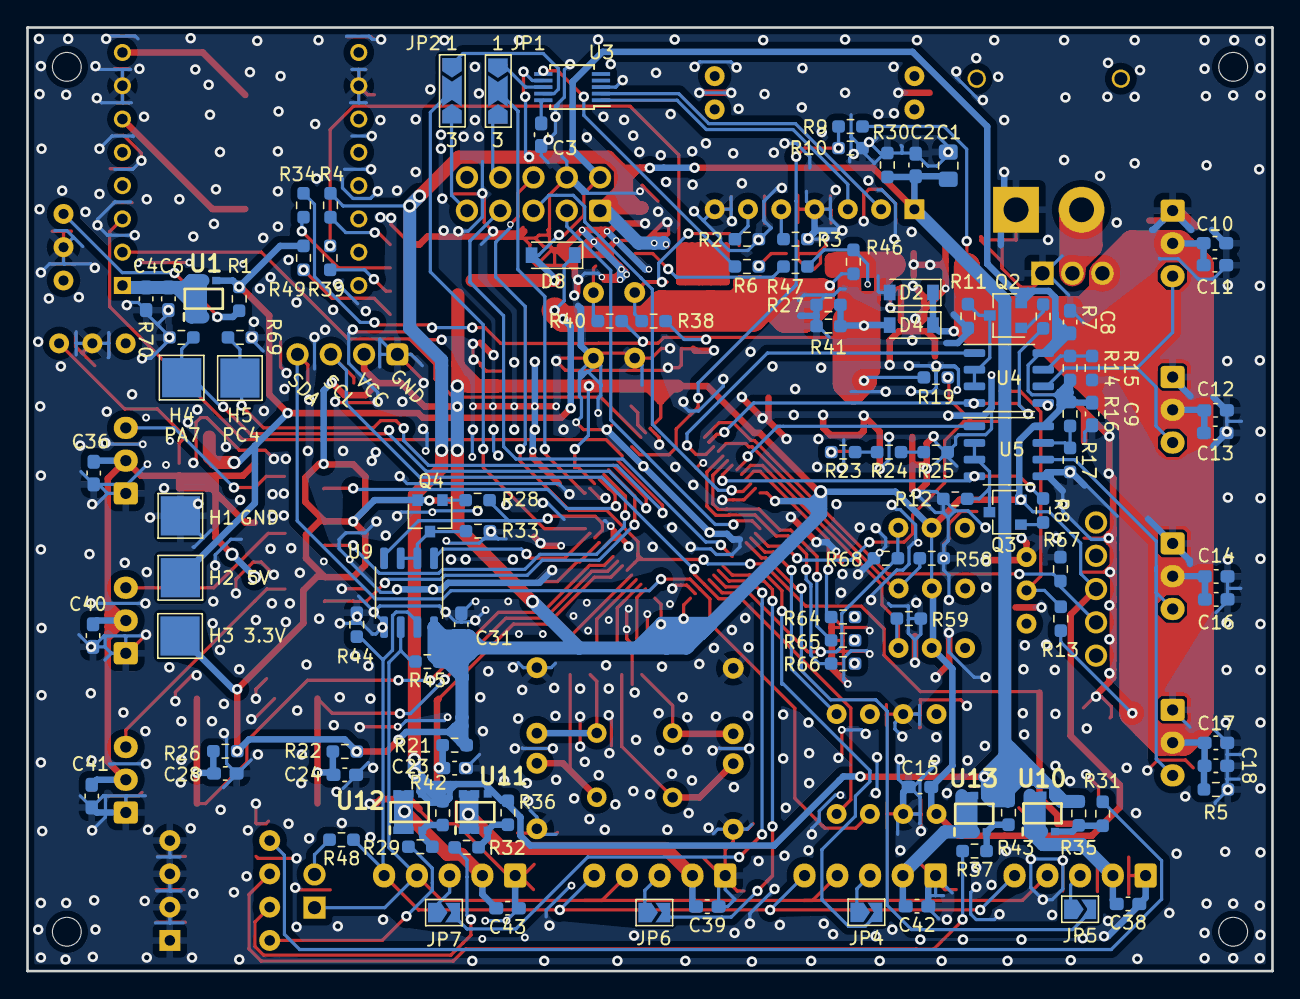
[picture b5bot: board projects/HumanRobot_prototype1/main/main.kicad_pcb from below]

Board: 2 copper layers, 95.0 x 72.0 mm, 200 parts (109 on the bottom side), 119 nets.
